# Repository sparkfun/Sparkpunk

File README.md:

SparkPunk - 555-Based Sound Generator
========================================

The SparkPunk kit Is a simple synthesizer that you assemble yourself.  If you're into circuit bending, there are also a bunch of mods you can do to the board.

The [hookup guide](https://learn.sparkfun.com/tutorials/sparkpunk-hookup-guide) has instructions for assembly, and recommends the first few mods you can consider.

This kit was created in Eagle v6.5.0, with design simulations run in [LTSpice](http://www.linear.com/designtools/software/#LTspice). 

Repository Contents
-------------------

* **/Hardware** - All Eagle design files (.brd, .sch, .STL)
* **/Simulations** - LTSpice schematics for simulation

Product Versions
----------------
* [KIT-11177](https://www.sparkfun.com/products/11177)- SparkPunk Sound Generator kit.

Version History
---------------
* [92ca0f047e](https://github.com/sparkfun/Sparkpunk/commit/92ca0f047e3397d55f9d692a53f35f9b94eaf454) PCB revision 1.3 
* [d7b850879f](https://github.com/sparkfun/Sparkpunk/commit/d7b850879f343ff84054743f3793c951a8b04aeb) PCB revision 1.2 
* [14a08d87a8](https://github.com/sparkfun/Sparkpunk/commit/14a08d87a8a0a1159d9d88a0d402fd1dced95e91) PCB revision 1.1 
* [5d9a28e00b](https://github.com/sparkfun/Sparkpunk/commit/5d9a28e00b7679d7cc441decd9c348f060b642cb) PCB revision 1.0

License Information
-------------------
The hardware is released under [Creative Commons ShareAlike 4.0 International](https://creativecommons.org/licenses/by-sa/4.0/).
The code is beerware; if you see me (or any other SparkFun employee) at the local, and you've found our code helpful, please buy us a round!

Distributed as-is; no warranty is given.

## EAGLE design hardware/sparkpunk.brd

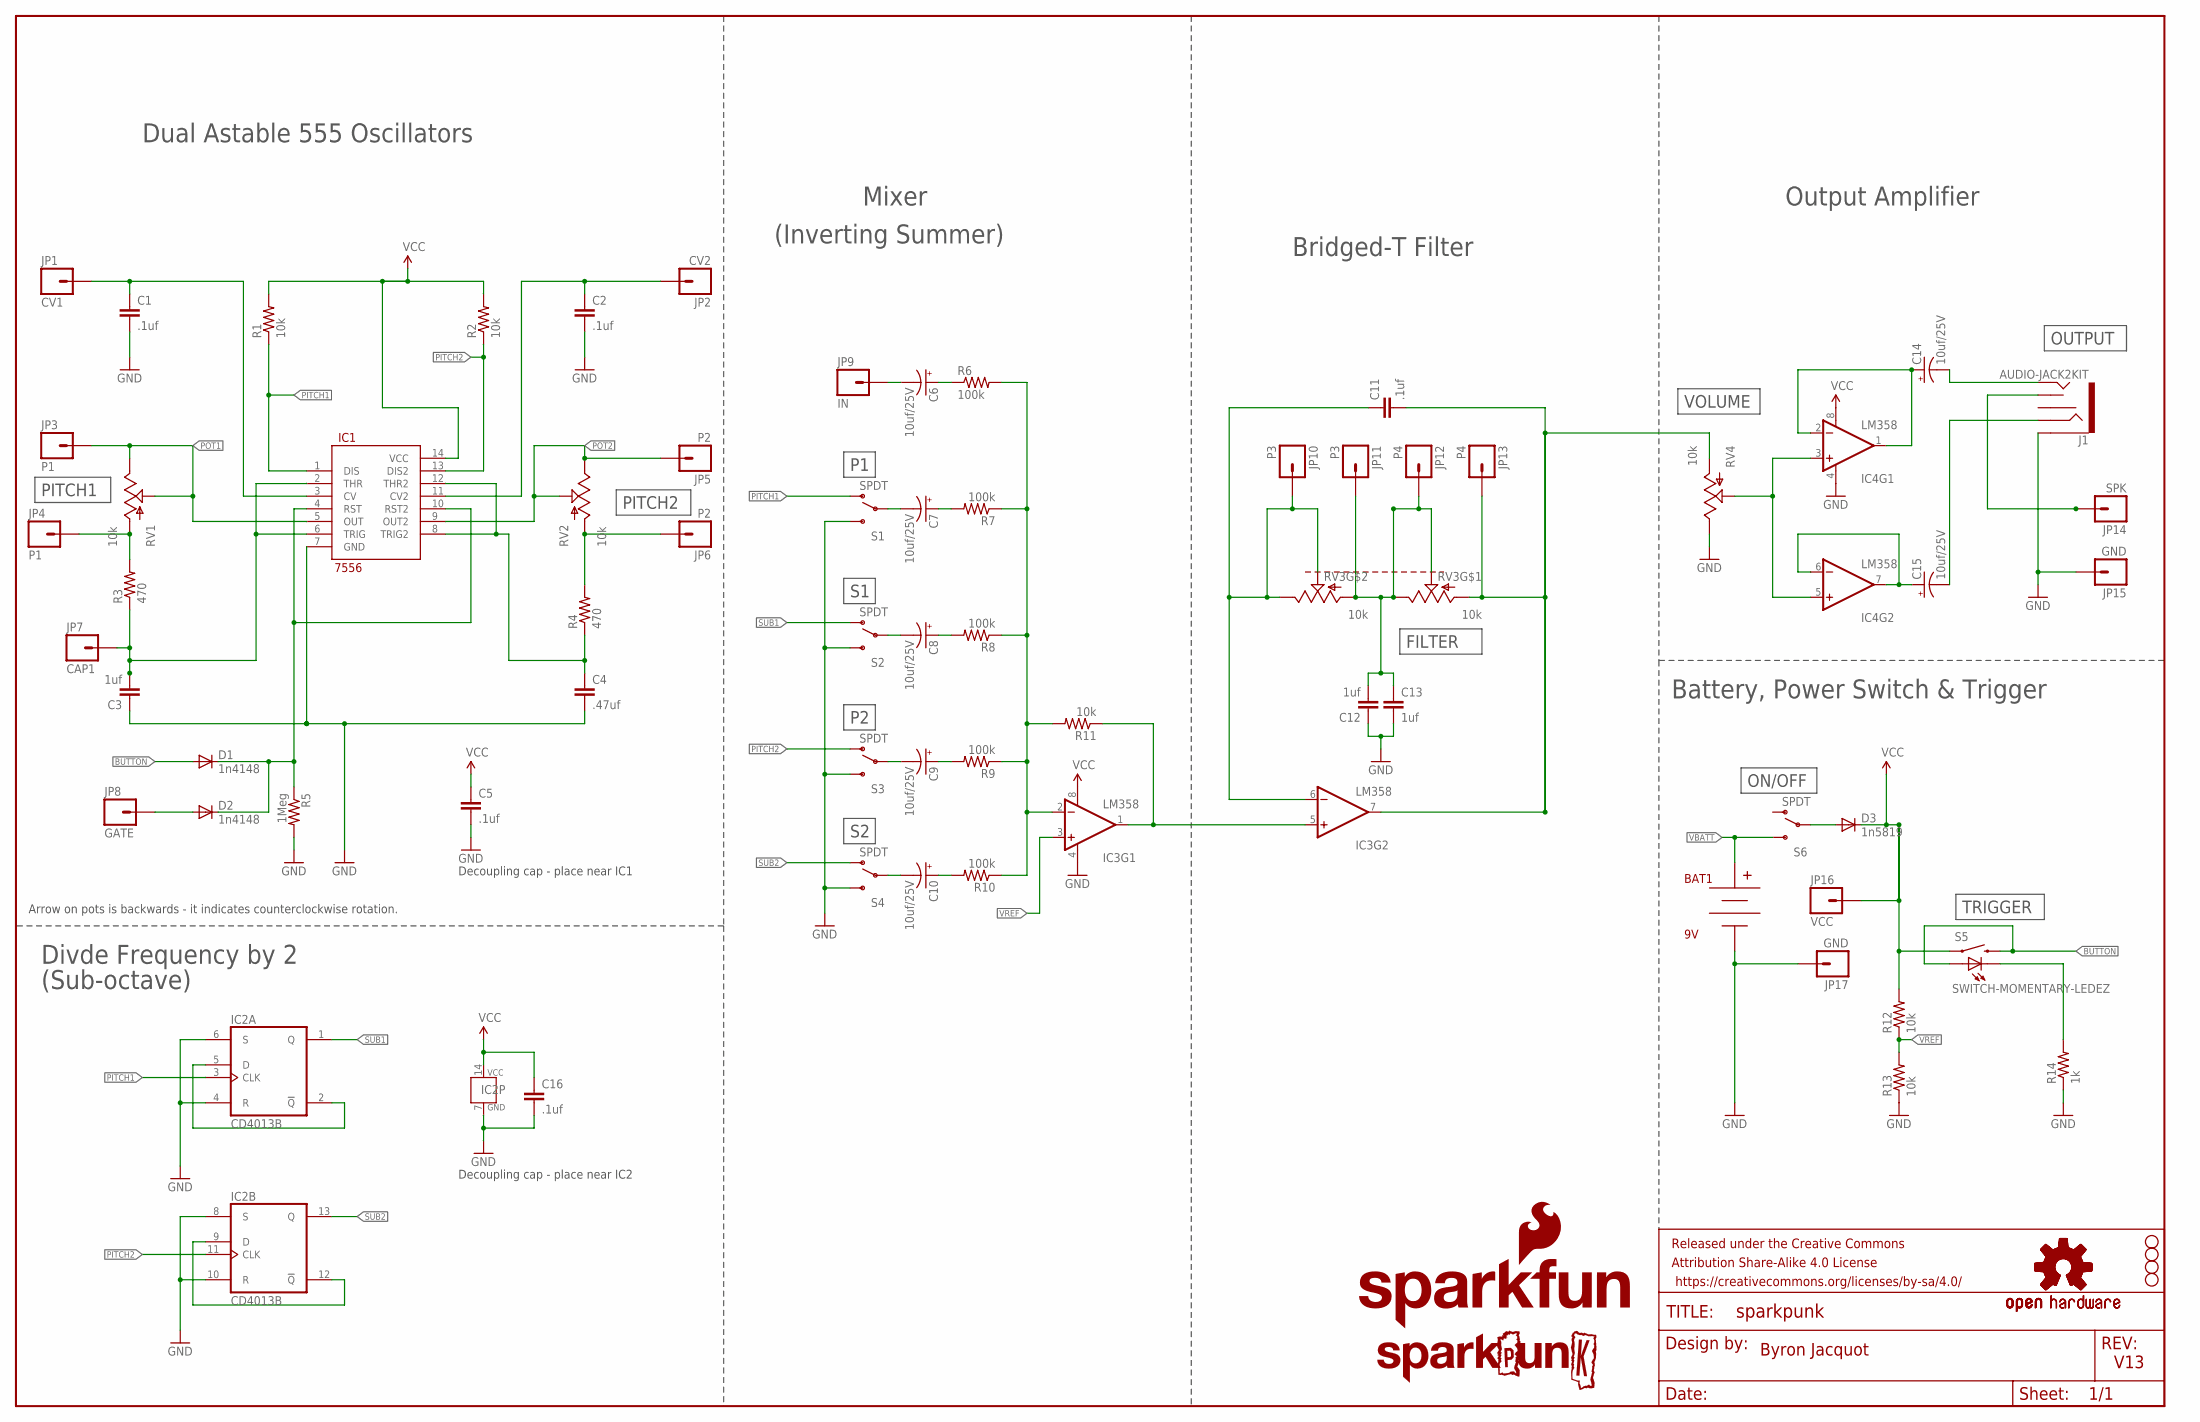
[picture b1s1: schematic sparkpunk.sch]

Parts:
BAT1: 9V; BC9VPC_KIT
C1, C2, C5, C11, C16: .1uf; CAP-PTH-SMALL-KIT
C3, C12, C13: 1uf; CAP-PTH-SMALL-KIT
C4: .47uf; CAP-PTH-SMALL-KIT
C6, C7, C8, C9, C10, C14, C15: 10uf/25V; CPOL-RADIAL-10UF-25V-KIT
D1, D2: 1n4148; DIODE-1N4148-KIT
D3: 1n5819; DIODE-1N4001-KIT
FRAME1: FRAME-LEDGER; CREATIVE_COMMONS
IC1: 7556; DIL14-KIT
IC2: CD4013B; DIL14-KIT
IC3, IC4: LM358; DIP08-KIT
J1: AUDIO-JACK2KIT; AUDIO-JACK-KIT
JP1: CV1; 1X01NS
JP2: CV2; 1X01NS
JP3, JP4: P1; 1X01NS
JP5, JP6: P2; 1X01NS
JP7: CAP1; 1X01NS
JP8: GATE; 1X01NS
JP9: IN; 1X01NS
JP10, JP11: P3; 1X01NS
JP12, JP13: P4; 1X01NS
JP14: SPK; 1X01NS
JP15, JP17: GND; 1X01NS
JP16: VCC; 1X01NS
LOGO1: SFE_LOGO_NAME_FLAME.2_INCH; SFE_LOGO_NAME_FLAME_.2
LOGO2: SPARKPUNK_LOGO.1INCH_TALL; SPARKPUNK_LOGO_.1
LOGO3, LOGO4: OSHW-LOGOM; OSHW-LOGO-M
R1, R2, R11, R12, R13: 10k; AXIAL-0.3EZ
R3, R4: 470; AXIAL-0.3EZ
R5: 1Meg; AXIAL-0.3EZ
R6, R7, R8, R9, R10: 100k; AXIAL-0.3EZ
R14: 1k; AXIAL-0.3EZ
RV1, RV2, RV4: 10k; ALPS_POT_KIT
RV3: 10k; POT_PANASONIC_DUAL_VERT_KIT
S1, S2, S3, S4, S6: SPDT; SWITCH-SPDT_KIT
S5: SWITCH-MOMENTARY-LEDEZ; TACTILE-PTH-LED-12MM-EZ
STANDOFF1, STANDOFF2, STANDOFF3, STANDOFF4: STAND-OFF

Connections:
BUTTON: D1.A, S5.2, S5.A
FILT-OUT: C11.2, IC3.7 (OUT), JP13.1, RV3.A3 (A), RV4.P$3 (A)
GND: BAT1.V-, C1.2, C2.2, C3.1, C4.2, C5.2, C12.1, C13.2, C16.2, IC1.7 (GND), IC2.4 (R), IC2.6 (S), IC2.7 (GND), IC2.8 (S), IC2.10 (R), IC3.4 (V-), IC4.4 (V-), J1.SLEEVE, JP15.1, JP17.1, R5.P$2 (2), R13.P$1 (1), R14.P$1 (1), RV4.P$1 (E), S1.3 (S), S2.3 (S), S3.3 (S), S4.3 (S)
N: IC4.3 (+IN), IC4.5 (+IN), RV4.P$2 (S)
unnamed: D2.A, JP8.1
unnamed: C4.1, IC1.8 (TRIG2), IC1.12 (THR2), R4.P$1 (1)
unnamed: D1.C, D2.C, IC1.4 (RST), IC1.10 (RST2), R5.P$1 (1)
unnamed: D3.A, S6.2
unnamed: JP6.1, R4.P$2 (2), RV2.P$3 (A)
unnamed: R14.P$2 (2), S5.C
unnamed: IC2.2 (!Q), IC2.5 (D)
unnamed: IC2.9 (D), IC2.12 (!Q)
unnamed: JP4.1, R3.P$2 (2), RV1.P$3 (A)
unnamed: C10.2 (-), S4.2
unnamed: J1.TSH, JP14.1
unnamed: C14.1 (+), IC4.1 (OUT), IC4.2 (-IN)
unnamed: C15.2 (-), J1.RING
unnamed: C10.1 (+), R10.P$2 (2)
unnamed: C9.1 (+), R9.P$2 (2)
unnamed: C9.2 (-), S3.2
unnamed: C6.2 (-), JP9.1
unnamed: C6.1 (+), R6.P$1 (1)
unnamed: C7.2 (-), S1.2
unnamed: C8.2 (-), S2.2
unnamed: C15.1 (+), IC4.6 (-IN), IC4.7 (OUT)
unnamed: IC3.2 (-IN), R6.P$2 (2), R7.P$1 (1), R8.P$1 (1), R9.P$1 (1), R10.P$1 (1), R11.P$2 (2)
unnamed: IC3.1 (OUT), IC3.5 (+IN), R11.P$1 (1)
unnamed: C8.1 (+), R8.P$2 (2)
unnamed: C7.1 (+), R7.P$2 (2)
unnamed: C14.2 (-), J1.TIP
unnamed: C11.1, IC3.6 (-IN), JP10.1, RV3.B1 (E), RV3.B2 (S)
unnamed: C12.2, C13.1, JP11.1, JP12.1, RV3.A1 (E), RV3.A2 (S), RV3.B3 (A)
PITCH1: IC1.1 (DIS), IC2.3 (CLK), R1.P$1 (1), S1.1 (O)
PITCH2: IC1.13 (DIS2), IC2.11 (CLK), R2.P$1 (1), S3.1 (O)
POT1: IC1.5 (OUT), JP3.1, RV1.P$1 (E), RV1.P$2 (S)
POT2: IC1.9 (OUT2), JP5.1, RV2.P$1 (E), RV2.P$2 (S)
SUB1: IC2.1 (Q), S2.1 (O)
SUB2: IC2.13 (Q), S4.1 (O)
VBATT: BAT1.V+, S6.3 (S)
VCAP1: C3.2, IC1.2 (THR), IC1.6 (TRIG), JP7.1, R3.P$1 (1)
VCC: C5.1, C16.1, D3.C, IC1.14 (VCC), IC2.14 (VCC), IC3.8 (V+), IC4.8 (V+), JP16.1, R1.P$2 (2), R2.P$2 (2), R12.P$2 (2), S5.4 (1)
VCC1: C2.1, IC1.11 (CV2), JP2.1
VCC2: C1.1, IC1.3 (CV), JP1.1
VREF: IC3.3 (+IN), R12.P$1 (1), R13.P$2 (2)

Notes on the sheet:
Byron Jacquot
V13
Arrow on pots is backwards - it indicates counterclockwise rotation.
Battery, Power Switch & Trigger
Dual Astable 555 Oscillators
Divde Frequency by 2
(Sub-octave)
Mixer
(Inverting Summer)
Bridged-T Filter
Output Amplifier
PITCH1
PITCH2
FILTER
VOLUME
OUTPUT
TRIGGER
Decoupling cap - place near IC1
Decoupling cap - place near IC2
ON/OFF

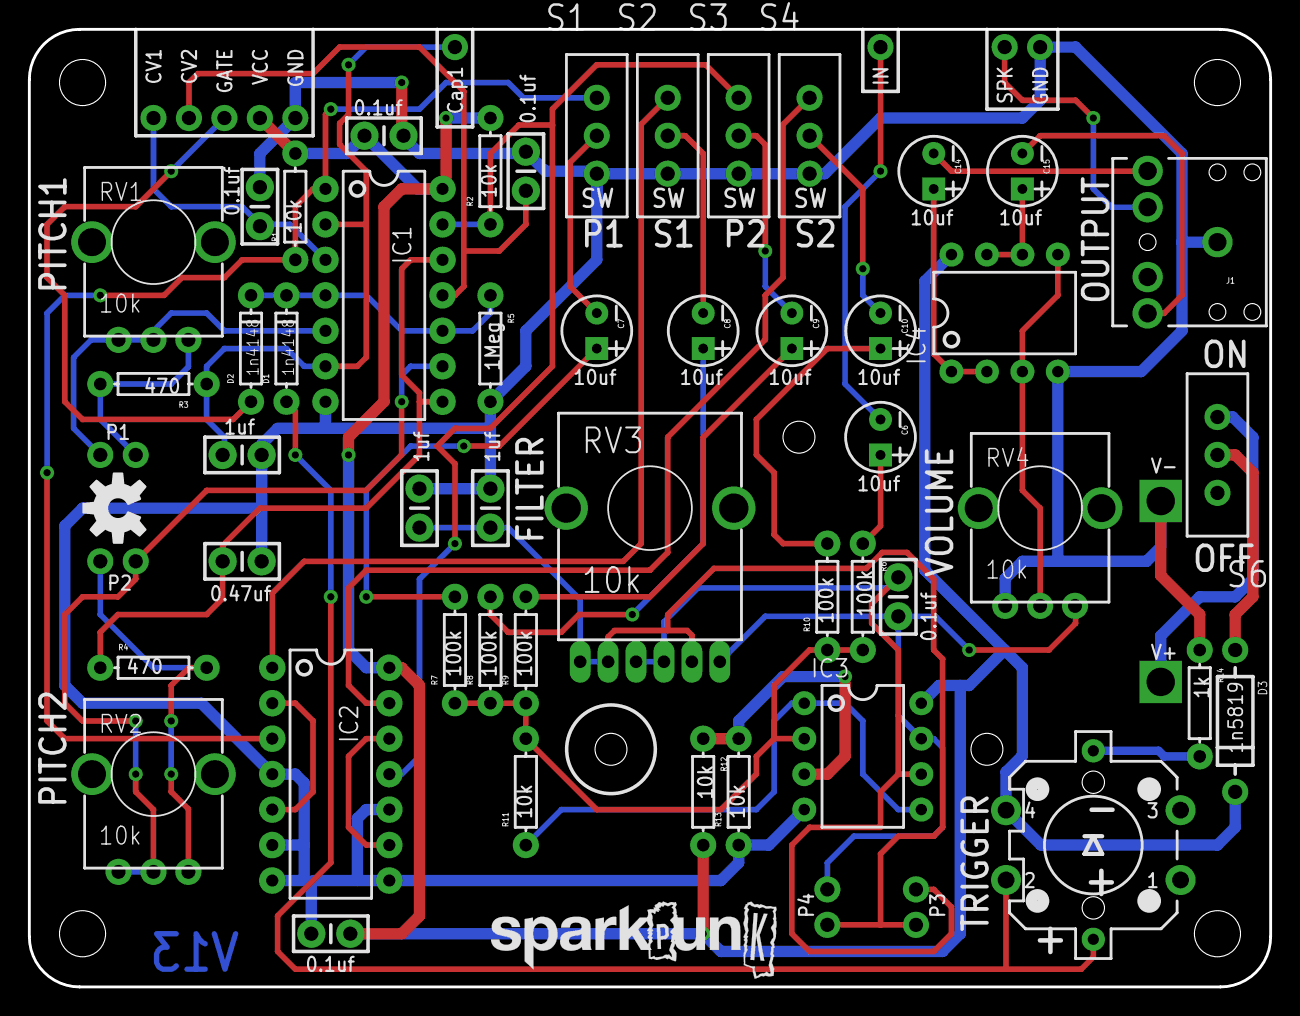
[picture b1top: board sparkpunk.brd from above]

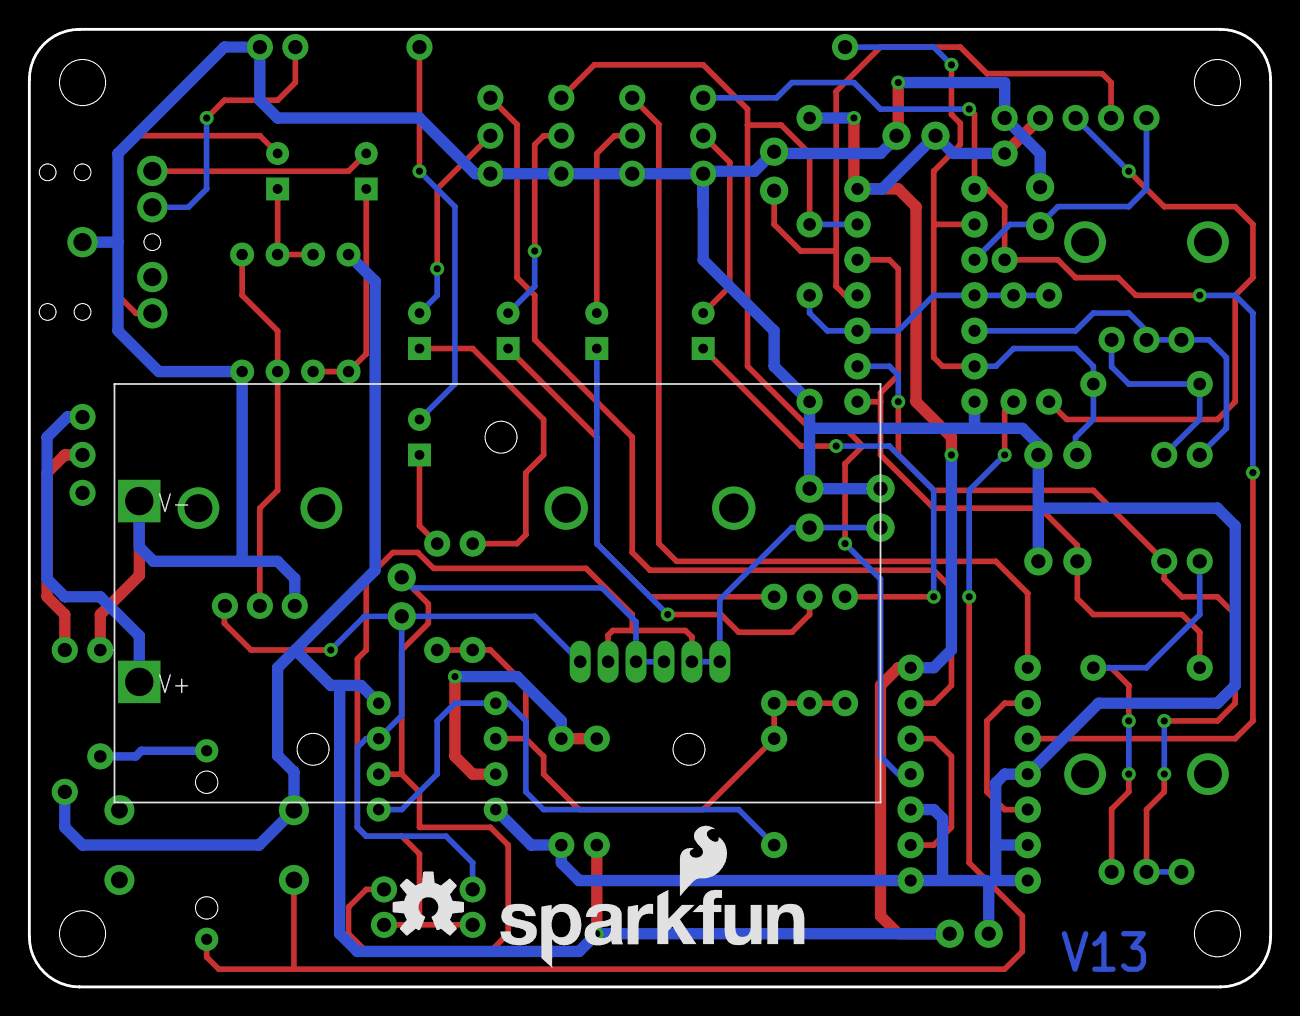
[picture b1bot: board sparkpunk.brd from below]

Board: 2 copper layers, 88.9 x 68.6 mm, 75 parts (3 on the bottom side), 44 nets.

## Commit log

2013-11-26 Initial files - gitignore and readme.
2013-11-26 Adding board files
2013-12-02 Updates following group review
2013-12-26 Updates from prototype evaluation
2013-12-26 Updating sparkpunk parts with in-house ID#s
2013-12-26 One more sparkle part number.
2014-01-03 Adding svg source for graphics
2014-03-25 Adding intermediate simulations.
    Piecemeal sims of mixer, filter comparison, etc.
2014-03-25 PCB update
    Redesigned some aspects of PCB, for tighter integration with the
    sequencer.
2014-04-25 Updated with feedback from beta builders.
2014-04-28 Ready for Reds
    Reviewed and ready to go.
2014-06-12 Updating readme for release
    Product going live - readme filled in with actual info, some
    reorganization.
2014-06-12 Adding oscillator sim.
    Found oscillator sim on my desktop, and updated it to represent the
    actual device.
2014-06-13 Adding SPICE temp files to .gitignore

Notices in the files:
parts and their libraries:
SparkFun-Aesthetics: Licensing: CC v3.0 Share-Alike You are welcome to use this library for commercial purposes.
SparkFun-Aesthetics: Released under the Creative Commons Attribution Share-Alike 4.0 License
SparkFun-Aesthetics: Released under the Creative Commons
